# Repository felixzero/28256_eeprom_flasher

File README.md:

# 28256_eeprom_flasher
Hardware and software for an EEPROM flasher for 28256 EEPROMs.

## How does it work?
- The electronics CAD files are in the `electronics`. You will need Kicad to open them.
- The 3d printed plastic enclosure CAD files are in the `mechanical` folder. You will need FreeCAD.
- The Arduino sketch is in the `firmware` folder.
- The Python script (to communicate with the flasher) is in the `software` folder.

## I just want it
Then you can simply download [the production files](production-files.zip):
- Send the `gerber.zip` file to a PCB manufacturer
- Use a 3d printer to print the two `.obj` files
- Checkout the Git repository to download the software

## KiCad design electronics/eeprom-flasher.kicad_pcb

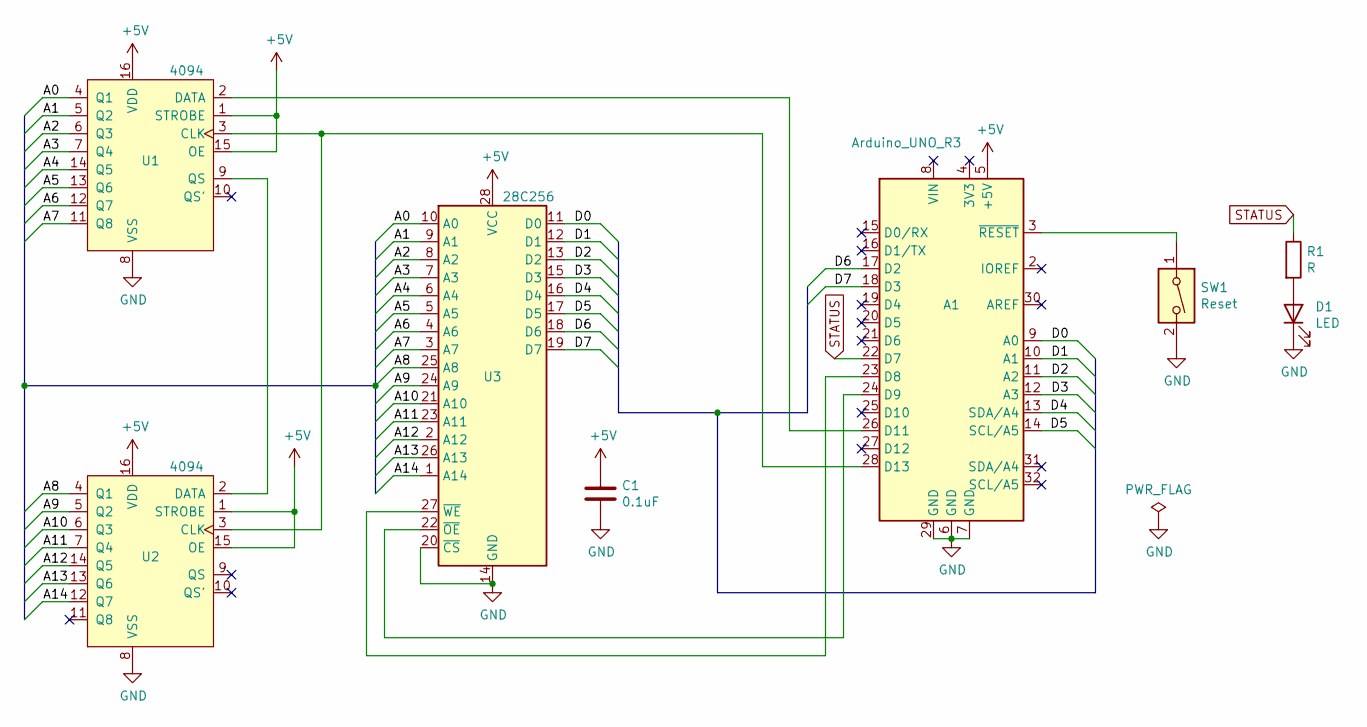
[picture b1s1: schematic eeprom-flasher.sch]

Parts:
A1: Arduino_UNO_R3
C1: 0.1uF; C_Rect_L7.2mm_W3.0mm_P5.00mm_FKS2_FKP2_MKS2_MKP2
D1: LED; LED_D3.0mm_FlatTop
R1: R; R_Axial_DIN0207_L6.3mm_D2.5mm_P2.54mm_Vertical
SW1: Reset; SW_PUSH_6mm
U1, U2: 4094; DIP-16_W7.62mm_LongPads
U3: 28C256; DIP_Socket-28_W11.9_W12.7_W15.24_W17.78_W18.5_3M_228-1277-0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

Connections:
+5V: A1.5 (+5V), C1.1, U1.1 (STROBE), U1.15 (OE), U1.16 (VDD), U2.1 (STROBE), U2.15 (OE), U2.16 (VDD), U3.28 (VCC)
/A0: U1.4 (Q1), U3.10 (A0)
/A1: U1.5 (Q2), U3.9 (A1)
/A2: U1.6 (Q3), U3.8 (A2)
/A3: U1.7 (Q4), U3.7 (A3)
/A4: U1.14 (Q5), U3.6 (A4)
/A5: U1.13 (Q6), U3.5 (A5)
/A6: U1.12 (Q7), U3.4 (A6)
/A7: U1.11 (Q8), U3.3 (A7)
/A8: U2.4 (Q1), U3.25 (A8)
/A9: U2.5 (Q2), U3.24 (A9)
/A10: U2.6 (Q3), U3.21 (A10)
/A11: U2.7 (Q4), U3.23 (A11)
/A12: U2.14 (Q5), U3.2 (A12)
/A13: U2.13 (Q6), U3.26 (A13)
/A14: U2.12 (Q7), U3.1 (A14)
/D0: A1.9 (A0), U3.11 (D0)
/D1: A1.10 (A1), U3.12 (D1)
/D2: A1.11 (A2), U3.13 (D2)
/D3: A1.12 (A3), U3.15 (D3)
/D4: A1.13 (SDA/A4), U3.16 (D4)
/D5: A1.14 (SCL/A5), U3.17 (D5)
/D6: A1.17 (D2), U3.18 (D6)
/D7: A1.18 (D3), U3.19 (D7)
GND: A1.6 (GND), A1.7 (GND), A1.29 (GND), C1.2, D1.1 (K), SW1.2, U1.8 (VSS), U2.8 (VSS), U3.14 (GND), U3.20 (~CS)
unnamed: A1.3 (~RESET), SW1.1
unnamed: A1.23 (D8), U3.27 (~WE)
unnamed: A1.24 (D9), U3.22 (~OE)
unnamed: A1.26 (D11), U1.2 (DATA)
unnamed: A1.28 (D13), U1.3 (CLK), U2.3 (CLK)
unnamed: D1.2 (A), R1.2
unnamed: U1.9 (QS), U2.2 (DATA)
STATUS: A1.22 (D7), R1.1

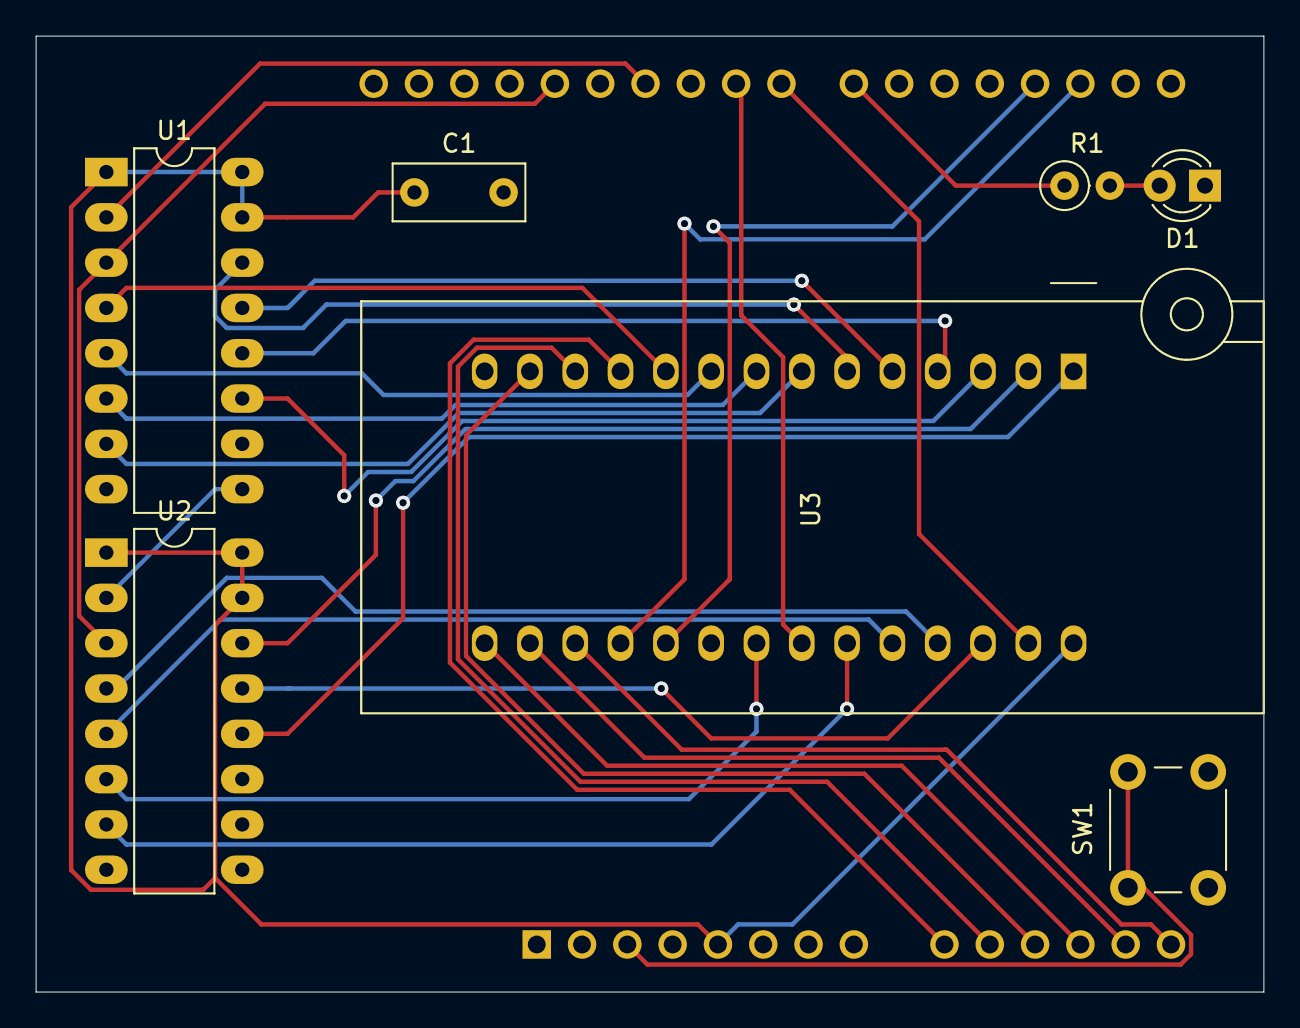
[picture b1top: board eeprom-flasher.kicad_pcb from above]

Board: 2 copper layers, 68.8 x 53.6 mm, 8 parts (1 on the bottom side), 33 nets.

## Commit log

2021-04-25 Create LICENSE
2021-04-25 Add photo
